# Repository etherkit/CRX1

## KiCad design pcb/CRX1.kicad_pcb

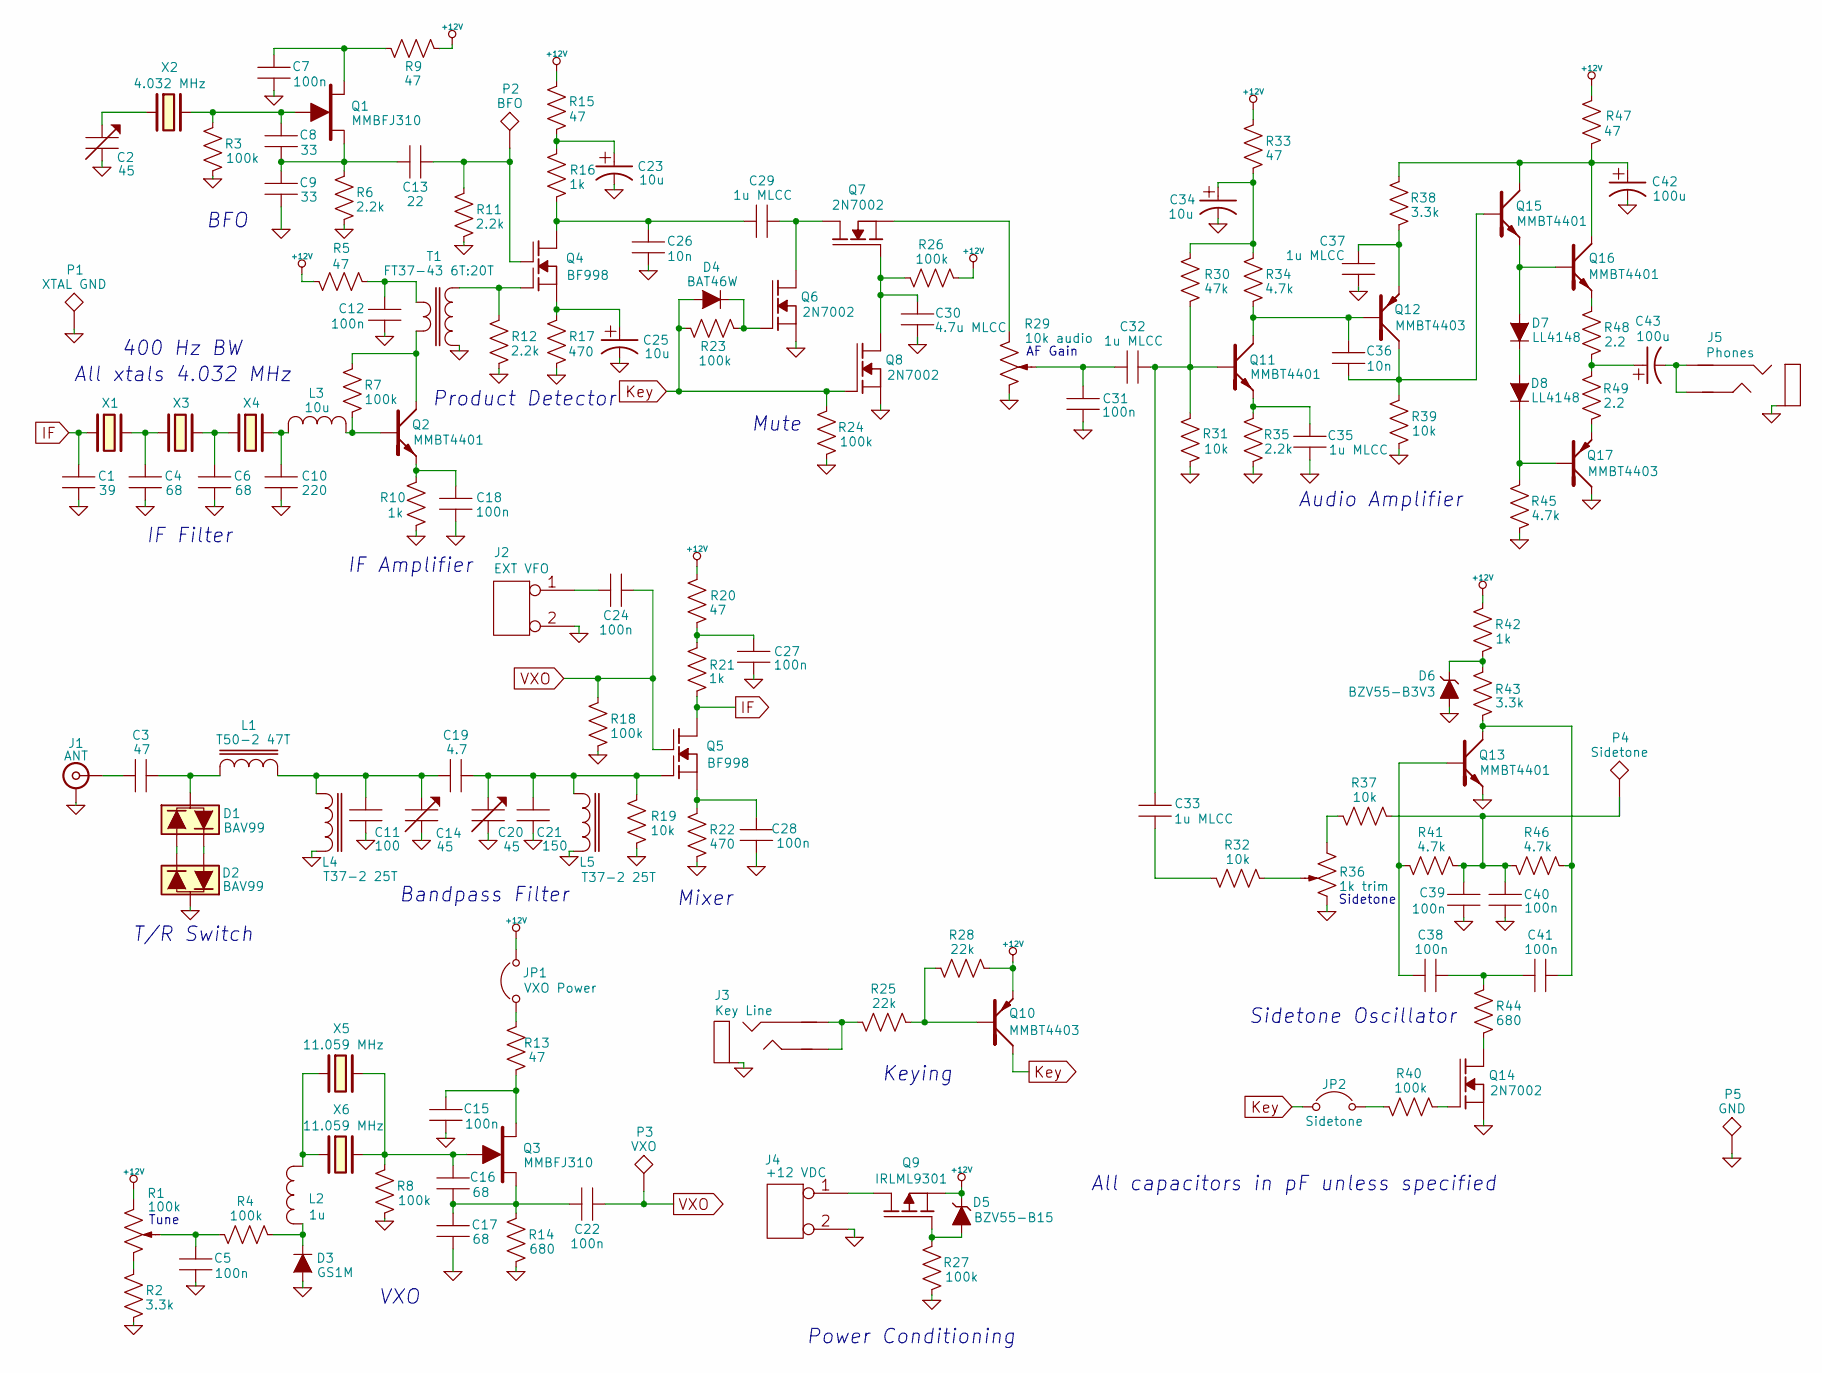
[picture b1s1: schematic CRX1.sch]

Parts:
C1: 39
C2, C14, C20: 45
C3: 47
C4, C6, C16, C17: 68
C5, C7, C12, C15, C18, C22, C24, C27, C28, C31, C38, C39, C40, C41: 100n
C8, C9: 33
C10: 220
C11: 100
C13: 22
C19: 4.7
C21: 150
C23, C25, C34: 10u
C26, C36: 10n
C29, C32, C33, C35, C37: 1u MLCC
C30: 4.7u MLCC
C42, C43: 100u
D1, D2: BAV99
D3: GS1M
D4: BAT46W
D5: BZV55-B15
D6: BZV55-B3V3
D7, D8: LL4148
J1: ANT
J2: EXT VFO
J3: Key Line
J4: +12 VDC
J5: Phones
JP1: VXO Power
JP2: Sidetone
L1: T50-2 47T
L2: 1u
L3: 10u
L4, L5: T37-2 25T
P1: XTAL GND
P2: BFO
P3: VXO
P4: Sidetone
P5: GND
Q1, Q3: MMBFJ310
Q2, Q11, Q13, Q15, Q16: MMBT4401
Q4, Q5: BF998
Q6, Q7, Q8, Q14: 2N7002
Q9: IRLML9301
Q10, Q12, Q17: MMBT4403
R1, R3, R4, R7, R8, R18, R23, R24, R26, R27, R40: 100k
R2, R38, R43: 3.3k
R5, R9, R13, R15, R20, R33, R47: 47
R6, R11, R12, R35: 2.2k
R10, R16, R21, R42: 1k
R14, R44: 680
R17, R22: 470
R19, R31, R32, R37, R39: 10k
R25, R28: 22k
R29: 10k audio
R30: 47k
R34, R41, R45, R46: 4.7k
R36: 1k trim
R48, R49: 2.2
T1: FT37-43 6T:20T
X1, X2, X3, X4: 4.032 MHz
X5, X6: 11.059 MHz

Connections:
+12V: D5.2 (K), JP1.2, Q9.1 (S), Q10.1 (E), R1.1, R5.1, R9.2, R15.1, R20.1, R26.2, R28.2, R33.1, R42.1, R47.1
IF: C1.1, Q5.2 (D), R21.2, X1.1
Key: D4.1 (A), JP2.1, Q8.2 (G), Q10.3 (C), R23.1, R24.1
unnamed: C11.1, C14.1, C19.1, L1.2, L4.1
unnamed: C19.2, C20.1, C21.1, L5.1, Q5.4 (G1), R19.1
unnamed: C28.1, Q5.1 (S), R22.1
unnamed: C10.1, L3.1, X4.2
unnamed: C6.1, X3.2, X4.1
unnamed: C3.1, J1.1 (In)
unnamed: C3.2, D1.3, L1.1
unnamed: D1.2, D2.1
unnamed: D1.1, D2.2
unnamed: C27.1, R20.2, R21.1
unnamed: C12.1, R5.2, T1.3
unnamed: Q2.3 (C), R7.1, T1.4
unnamed: C8.2, C9.1, C13.1, Q1.1 (S), R6.1
unnamed: C7.1, Q1.3 (D), R9.1
unnamed: C8.1, Q1.2 (G), R3.1, X2.2
unnamed: C2.1, X2.1
unnamed: C4.1, X1.2, X3.1
unnamed: L3.2, Q2.2 (B), R7.2
unnamed: C18.1, Q2.1 (E), R10.1
unnamed: C15.1, Q3.3 (D), R13.2
unnamed: Q10.2 (B), R25.2, R28.1
unnamed: L2.1, X5.1, X6.1
unnamed: J3.1, J3.2, R25.1
unnamed: C24.1, J2.1
unnamed: D3.2 (K), L2.2, R4.2
unnamed: C5.1, R1.2, R4.1
unnamed: R1.3, R2.1
unnamed: J4.1, Q9.3 (D)
unnamed: C43.2, J5.1, J5.2
unnamed: JP1.1, R13.1
unnamed: C16.1, Q3.2 (G), R8.1, X5.2, X6.2
unnamed: C16.2, C17.1, C22.1, Q3.1 (S), R14.1
unnamed: C33.2, R32.1
unnamed: C37.1, Q12.1 (E), R38.2
unnamed: C32.2, C33.1, Q11.2 (B), R30.2, R31.1
unnamed: C31.1, C32.1, R29.2
unnamed: C35.1, Q11.1 (E), R35.1
unnamed: C36.1, Q11.3 (C), Q12.2 (B), R34.2
unnamed: C34.1, R30.1, R33.2, R34.1
unnamed: R36.1, R37.1
unnamed: C39.1, C40.1, P4.1, R37.2, R41.2, R46.1
unnamed: R32.2, R36.2
unnamed: JP2.2, R40.1
unnamed: C38.1, Q13.2 (B), R41.1
unnamed: C41.2, Q13.3 (C), R43.2, R46.2
unnamed: Q14.2 (G), R40.2
unnamed: Q14.3 (D), R44.2
unnamed: C36.2, Q12.3 (C), Q15.2 (B), R39.1
unnamed: C43.1, R48.2, R49.1
unnamed: Q17.1 (E), R49.2
unnamed: D8.2 (K), Q17.2 (B), R45.1
unnamed: Q16.1 (E), R48.1
unnamed: D7.1 (A), Q15.1 (E), Q16.2 (B)
unnamed: C42.1, Q15.3 (C), Q16.3 (C), R38.1, R47.2
unnamed: D7.2 (K), D8.1 (A)
unnamed: C13.2, P2.1, Q4.3 (G2), R11.1
unnamed: D4.2 (K), Q6.2 (G), R23.2
unnamed: C29.2, Q6.3 (D), Q7.3 (D)
unnamed: C23.1, R15.2, R16.1
unnamed: Q4.4 (G1), R12.1, T1.1
unnamed: C26.1, C29.1, Q4.2 (D), R16.2
unnamed: C25.1, Q4.1 (S), R17.1
unnamed: C38.2, C41.1, R44.1
unnamed: Q7.1 (S), R29.1
unnamed: D6.2 (K), R42.2, R43.1
unnamed: C30.1, Q7.2 (G), Q8.3 (D), R26.1
VXO: C22.2, C24.2, P3.1, Q5.3 (G2), R18.1

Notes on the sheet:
All capacitors in pF unless specified
400 Hz BW
All xtals 4.032 MHz
Tune
AF Gain
VXO
Keying
Sidetone Oscillator
T/R Switch
Bandpass Filter
Mixer
IF Filter
IF Amplifier
Product Detector
Mute
Audio Amplifier
Sidetone
Power Conditioning
BFO

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
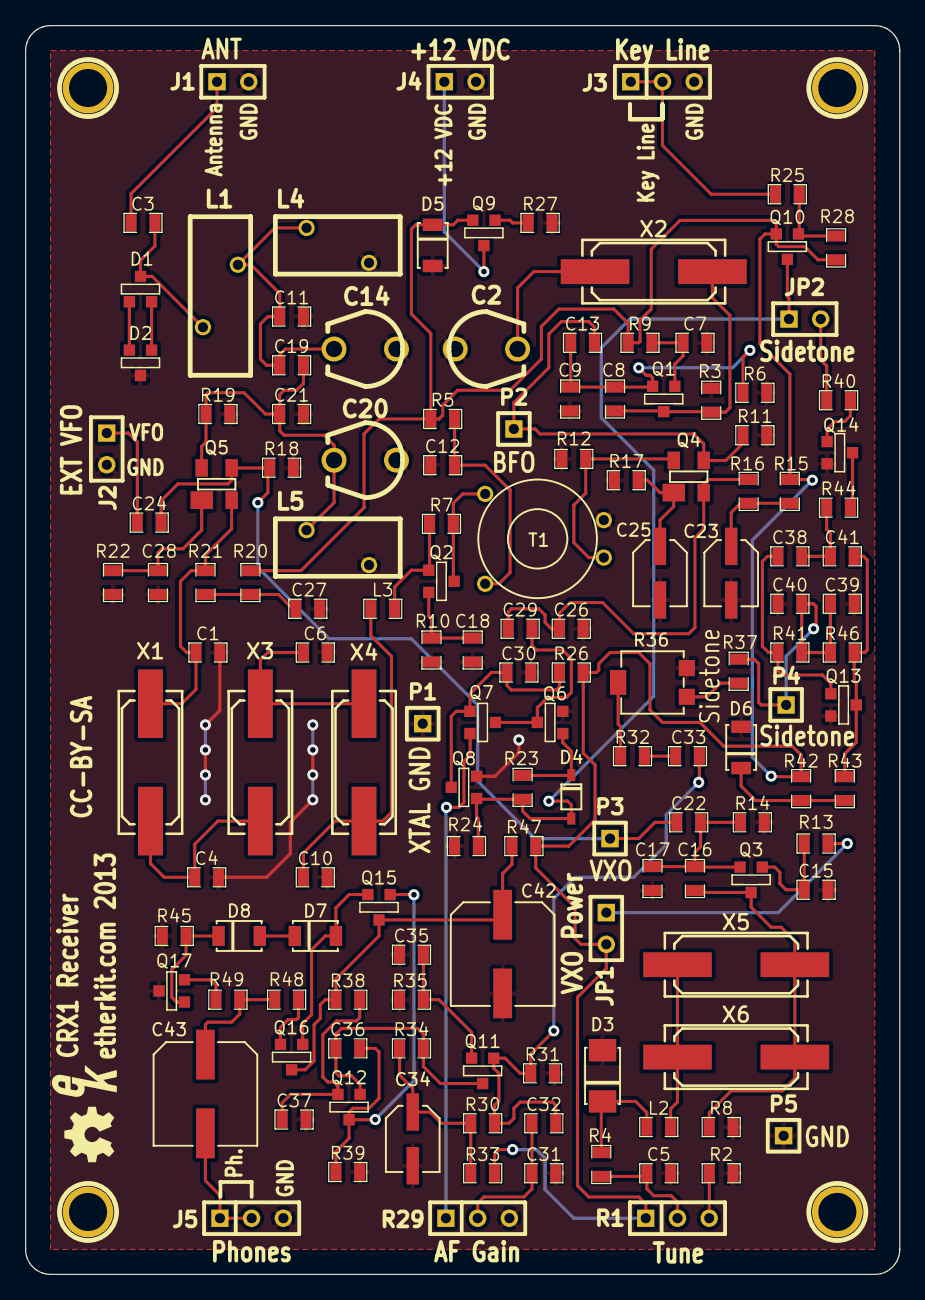
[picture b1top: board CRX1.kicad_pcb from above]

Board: 2 copper layers, 70.0 x 100.0 mm, 146 parts (0 on the bottom side), 72 nets.

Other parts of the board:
1PIN, 1PIN#2, 1PIN#3, 1PIN#4: P***; 1pin
Ref**: Val**; EtherkitLogoSmall

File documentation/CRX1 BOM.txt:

CRX1 BOM
Etherkit
8 Jun 2013

| Part (marking)                  | Qty  | Ref                            | P/N
======================================================================================================
Capacitors (all values pF unless specified)
| 4.7                               1      C19
| 22                                1      C13
| 33                                2      C8, C9
| 39                                1      C1
| 45 trim                           3      C2, C14, C20
| 47                                1      C3       
| 68                                4      C4, C6, C16, C17
| 100                               1      C11
| 150                               1      C21
| 220                               1      C10
| 10n                               2      C26, C36   
| 100n                              14     C5, C7, C12, C15, C18, C22,
                                           C24, C27, C28, C31, C38,
                                           C39, C40, C41
| 1u MLCC                           5      C29, C32, C33, C35, C37        
| 4.7u MLCC                         1      C30       
| 10u electrolytic                  3      C23, C25, C34       
| 100u electrolytic                 2      C42, C43            

Diodes
| BAT46W                            1      D4        
| BAV99                             2      D1, D2
| BZV55-B3V3                        1      D6       
| BZV55-B15                         1      D5
| GS1M                              1      D3
| LL4148                            2      D7, D8

Connectors        
| 3.5 mm stereo                     2      J3, J5                           Kobiconn 161-3402-E
| 2.1 mm barrel jack - +12VDC       1      J4                               Kobiconn 163-4304-E
| BNC                               1      J1                               TE 227754-2

Inductors
| 1u                                1      L2
| 10u                               1      L3        
| T37-2 25T                         2      L4, L5
| T50-2 47T                         1      L1   

Transistors       
| 2N7002                            4      Q6, Q7, Q8, Q14
| BF998                             2      Q4, Q5       
| MMBFJ310                          2      Q1, Q3
| MMBT4401                          5      Q11, Q13, Q15, Q16, Q2
| MMBT4403                          3      Q10, Q12, Q17        
| IRLML9301                         1      Q9       

Resistors (all resistors 0.1 watt 0805 unless specified)
| 2.2                               2      R48, R49
| 47                                7      R5, R9, R13, R15, R20, R33,
                                           R47
| 470                               2      R17, R22
| 680                               2      R14, R44
| 1k                                4      R10, R16, R21, R42
| 2.2k                              4      R6, R11, R12, R35
| 3.3k                              3      R2, R38, R43
| 4.7k                              4      R34, R41, R45, R46
| 10k                               5      R19, R31, R32, R37, R39
| 22k                               2      R25, R28
| 47k                               1      R30
| 100k                              10     R3, R4, R7, R8, R18, R23,
                                           R24, R26, R27, R40    

Potentiometers
| 1k trim                           1      R36                              Vishay TS53YL102MR10
| 10k audio                         1      R29                              Alpha RV16AF-10-15S1-A10K
| 100k linear                       1      R1                               Alpha RV16AF-10-15R1-B100K

Transformers
| FT37-43 6T:20T                    1      T1

Crystals        
| 4.032 MHz                         4      X1, X2, X3, X4                   ECS-40.3-20-5PX-TR
| 11.059 MHz                        2      X5, X6                           Abracon ABLS-11.0592MHZ-B4-T

Miscellaneous
| Red Magnet Wire, 28 AWG (feet)    5
| Green Magnet Wire, 28 AWG (feet)  1
| PCB

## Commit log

2013-07-27 Rev A Production

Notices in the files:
pcb/CRX1.kicad_pcb:
Creative Commons License CC-BY-SA
CC-BY-SA
